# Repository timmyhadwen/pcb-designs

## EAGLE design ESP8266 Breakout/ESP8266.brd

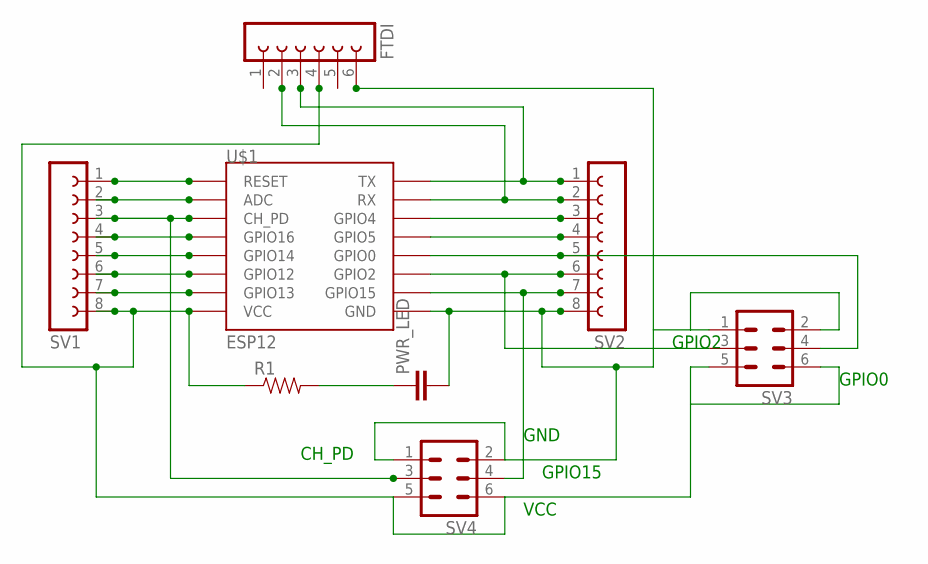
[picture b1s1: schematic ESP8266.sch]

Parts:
FTDI: FE06-1; FE06
PWR_LED: CAP0805; 0805
R1: RESISTOR0805-RES; 0805
SV1, SV2: FE08-1; FE08
SV3, SV4: MA03-2
U$1: ESP12

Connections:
GND: FTDI.6, PWR_LED.2, SV2.8, SV3.1, SV3.2, SV4.1, SV4.2, U$1.GND
unnamed: SV1.3, SV4.3, U$1.CH_PD
unnamed: SV1.1, U$1.RESET
unnamed: SV1.6, U$1.GPIO12
unnamed: SV1.5, U$1.GPIO14
unnamed: SV1.4, U$1.GPIO16
unnamed: SV1.7, U$1.GPIO13
unnamed: SV1.2, U$1.ADC
unnamed: FTDI.2, SV2.2, U$1.RX
unnamed: SV2.3, U$1.GPIO4
unnamed: SV2.4, U$1.GPIO5
unnamed: SV2.5, SV3.4, U$1.GPIO0
unnamed: SV2.6, SV3.3, U$1.GPIO2
unnamed: SV2.7, SV4.4, U$1.GPIO15
unnamed: FTDI.3, SV2.1, U$1.TX
unnamed: PWR_LED.1, R1.2
VCC: FTDI.4, R1.1, SV1.8, SV3.5, SV3.6, SV4.5, SV4.6, U$1.VCC

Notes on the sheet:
GND
VCC
CH_PD
GPIO15
GPIO0
GPIO2

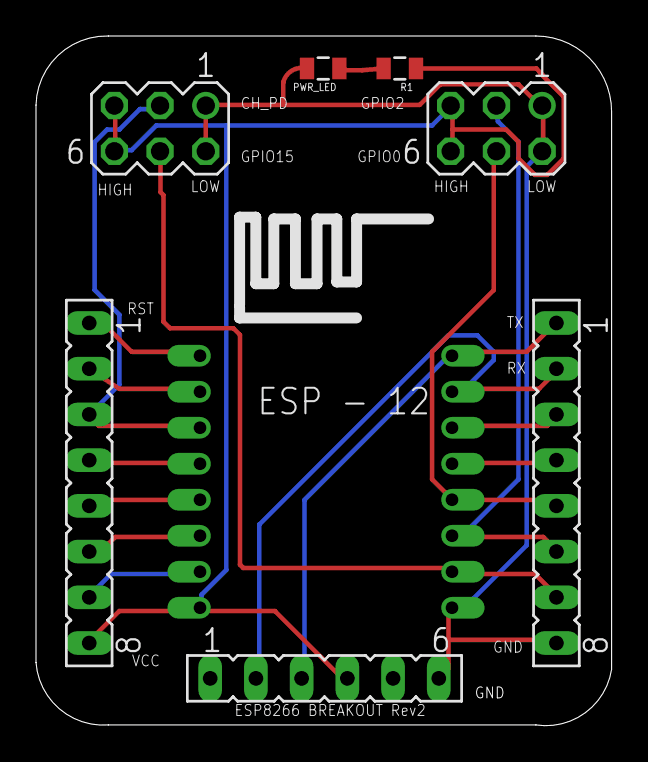
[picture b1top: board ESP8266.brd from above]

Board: 2 copper layers, 32.0 x 38.3 mm, 8 parts (0 on the bottom side), 17 nets.

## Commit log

2015-06-13 Adding some libs
2015-06-13 Added gitignore and ESP8266 breakout

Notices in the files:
parts and their libraries:
SparkFun-Passives: Licensing: Creative Commons ShareAlike 4.0 International - https://creativecommons.org/licenses/by-sa/4.0
